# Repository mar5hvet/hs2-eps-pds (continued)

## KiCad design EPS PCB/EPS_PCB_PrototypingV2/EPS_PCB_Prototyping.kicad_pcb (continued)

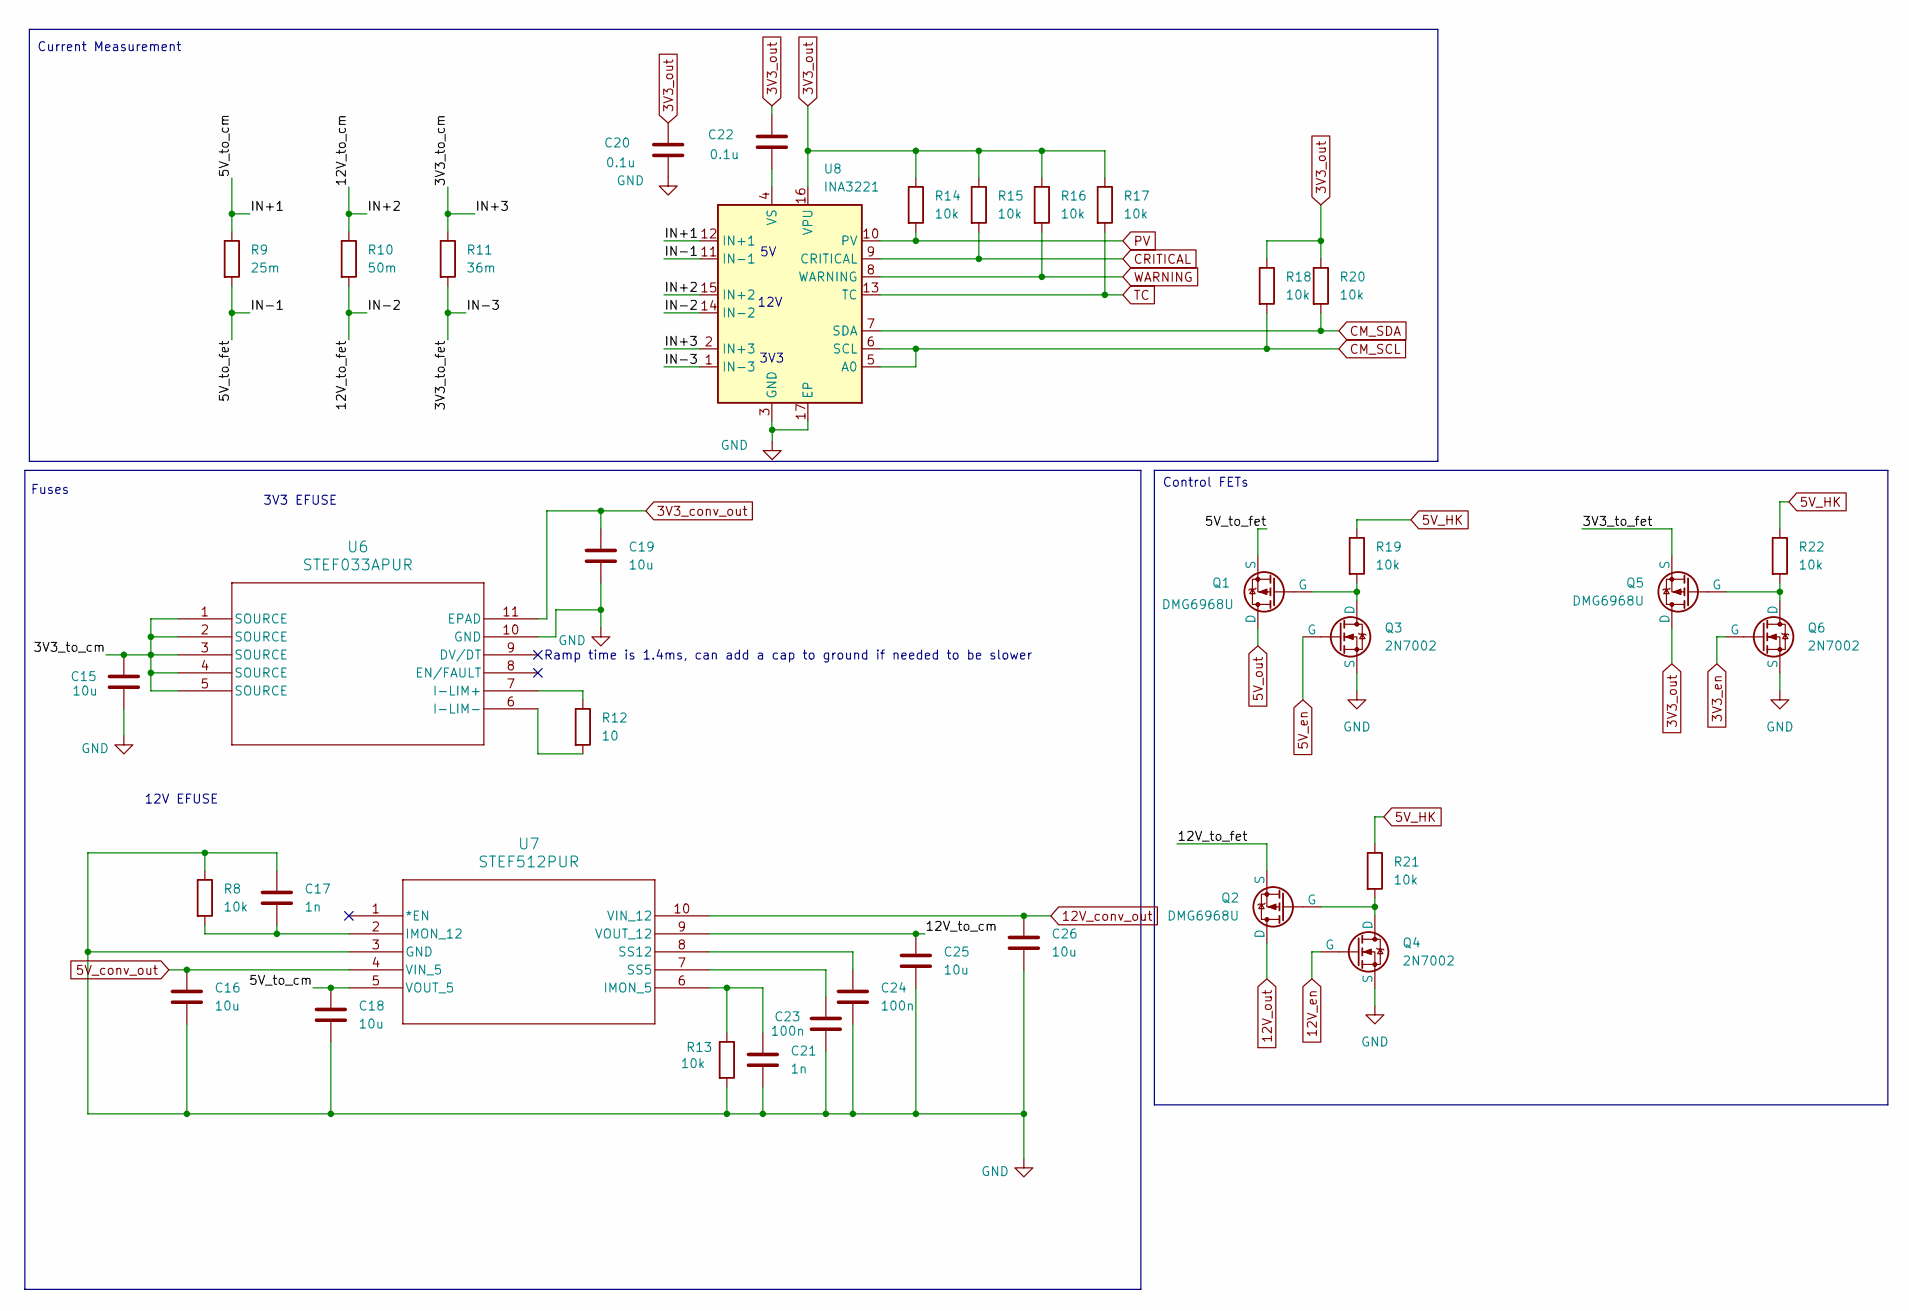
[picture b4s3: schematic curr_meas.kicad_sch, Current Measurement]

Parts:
C15, C16, C18, C19, C25, C26: 10u; C_0603_1608Metric
C17, C21: 1n; C_0603_1608Metric
C20, C22: 0.1u; C_0603_1608Metric
C23, C24: 100n; C_0603_1608Metric
Q1, Q2, Q5: DMG6968U; SOT-23-3
Q3, Q4, Q6: 2N7002; SOT-23-3
R8, R13, R14, R15, R16, R17, R18, R20: 10k; R_0603_1608Metric
R9: 25m; RES_VISHAY_WSLP2512_A_VIS
R10: 50m; RES_VISHAY_WSLP2512_A_VIS
R11: 36m; RES_VISHAY_WSLP2512_A_VIS
R12: 10; R_0603_1608Metric
R19, R21, R22: 10k; R_1206_3216Metric
U6: STEF033APUR; STEF033
U7: STEF512PUR; QFN10_2X3_STM-L
U8: INA3221; Texas_RGV0016A_VQFN-16-1EP_4x4mm_P0.65mm_EP2.1x2.1mm

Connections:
3V3_conv_out: C19.1, U6.11 (EPAD); also elsewhere on the board
3V3_en: Q6.2 (G); also elsewhere on the board
3V3_out: C20.1, C22.1, Q5.1 (D), R14.1, R15.1, R16.1, R17.1, R18.1, R20.1, U8.16 (VPU); also elsewhere on the board
5V_HK: R19.1, R21.1, R22.1; also elsewhere on the board
5V_conv_out: C16.1, U7.4 (VIN_5); also elsewhere on the board
5V_en: Q3.2 (G); also elsewhere on the board
5V_out: Q1.1 (D); also elsewhere on the board
12V_conv_out: C26.1, U7.10 (VIN_12); also elsewhere on the board
12V_en: Q4.2 (G); also elsewhere on the board
12V_out: Q2.1 (D); also elsewhere on the board
/Curr_meas/3V3_to_cm: C15.1, R11.1, U6.1 (SOURCE), U6.2 (SOURCE), U6.3 (SOURCE), U6.4 (SOURCE), U6.5 (SOURCE), U8.2 (IN+3)
/Curr_meas/3V3_to_fet: Q5.3 (S), R11.2, U8.1 (IN-3)
/Curr_meas/5V_to_cm: C18.1, R9.1, U7.5 (VOUT_5), U8.12 (IN+1)
/Curr_meas/5V_to_fet: Q1.3 (S), R9.2, U8.11 (IN-1)
/Curr_meas/12V_to_cm: C25.1, R10.1, U7.9 (VOUT_12), U8.15 (IN+2)
/Curr_meas/12V_to_fet: Q2.3 (S), R10.2, U8.14 (IN-2)
CM_SCL: R18.2, U8.5 (A0), U8.6 (SCL); also elsewhere on the board
CM_SDA: R20.2, U8.7 (SDA); also elsewhere on the board
CRITICAL: R15.2, U8.9 (CRITICAL); also elsewhere on the board
GND: C15.2, C16.2, C17.1, C18.2, C19.2, C20.2, C21.2, C23.2, C24.2, C25.2, C26.2, Q3.3 (S), Q4.3 (S), Q6.3 (S), R8.1, R13.2, U6.10 (GND), U7.3 (GND), U8.3 (GND), U8.17 (EP); also elsewhere on the board
unnamed: Q1.2 (G), Q3.1 (D), R19.2
unnamed: Q2.2 (G), Q4.1 (D), R21.2
unnamed: Q5.2 (G), Q6.1 (D), R22.2
unnamed: R12.1, U6.7 (I-LIM+)
unnamed: R12.2, U6.6 (I-LIM-)
unnamed: C21.1, R13.1, U7.6 (IMON_5)
unnamed: C17.2, R8.2, U7.2 (IMON_12)
unnamed: C23.1, U7.7 (SS5)
unnamed: C24.1, U7.8 (SS12)
unnamed: C22.2, U8.4 (VS)
PV: R14.2, U8.10 (PV); also elsewhere on the board
TC: R17.2, U8.13 (TC)
WARNING: R16.2, U8.8 (WARNING); also elsewhere on the board

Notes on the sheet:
12V
Current Measurement
3V3 EFUSE
3V3
Ramp time is 1.4ms, can add a cap to ground if needed to be slower
12V EFUSE
Control FETs
Fuses

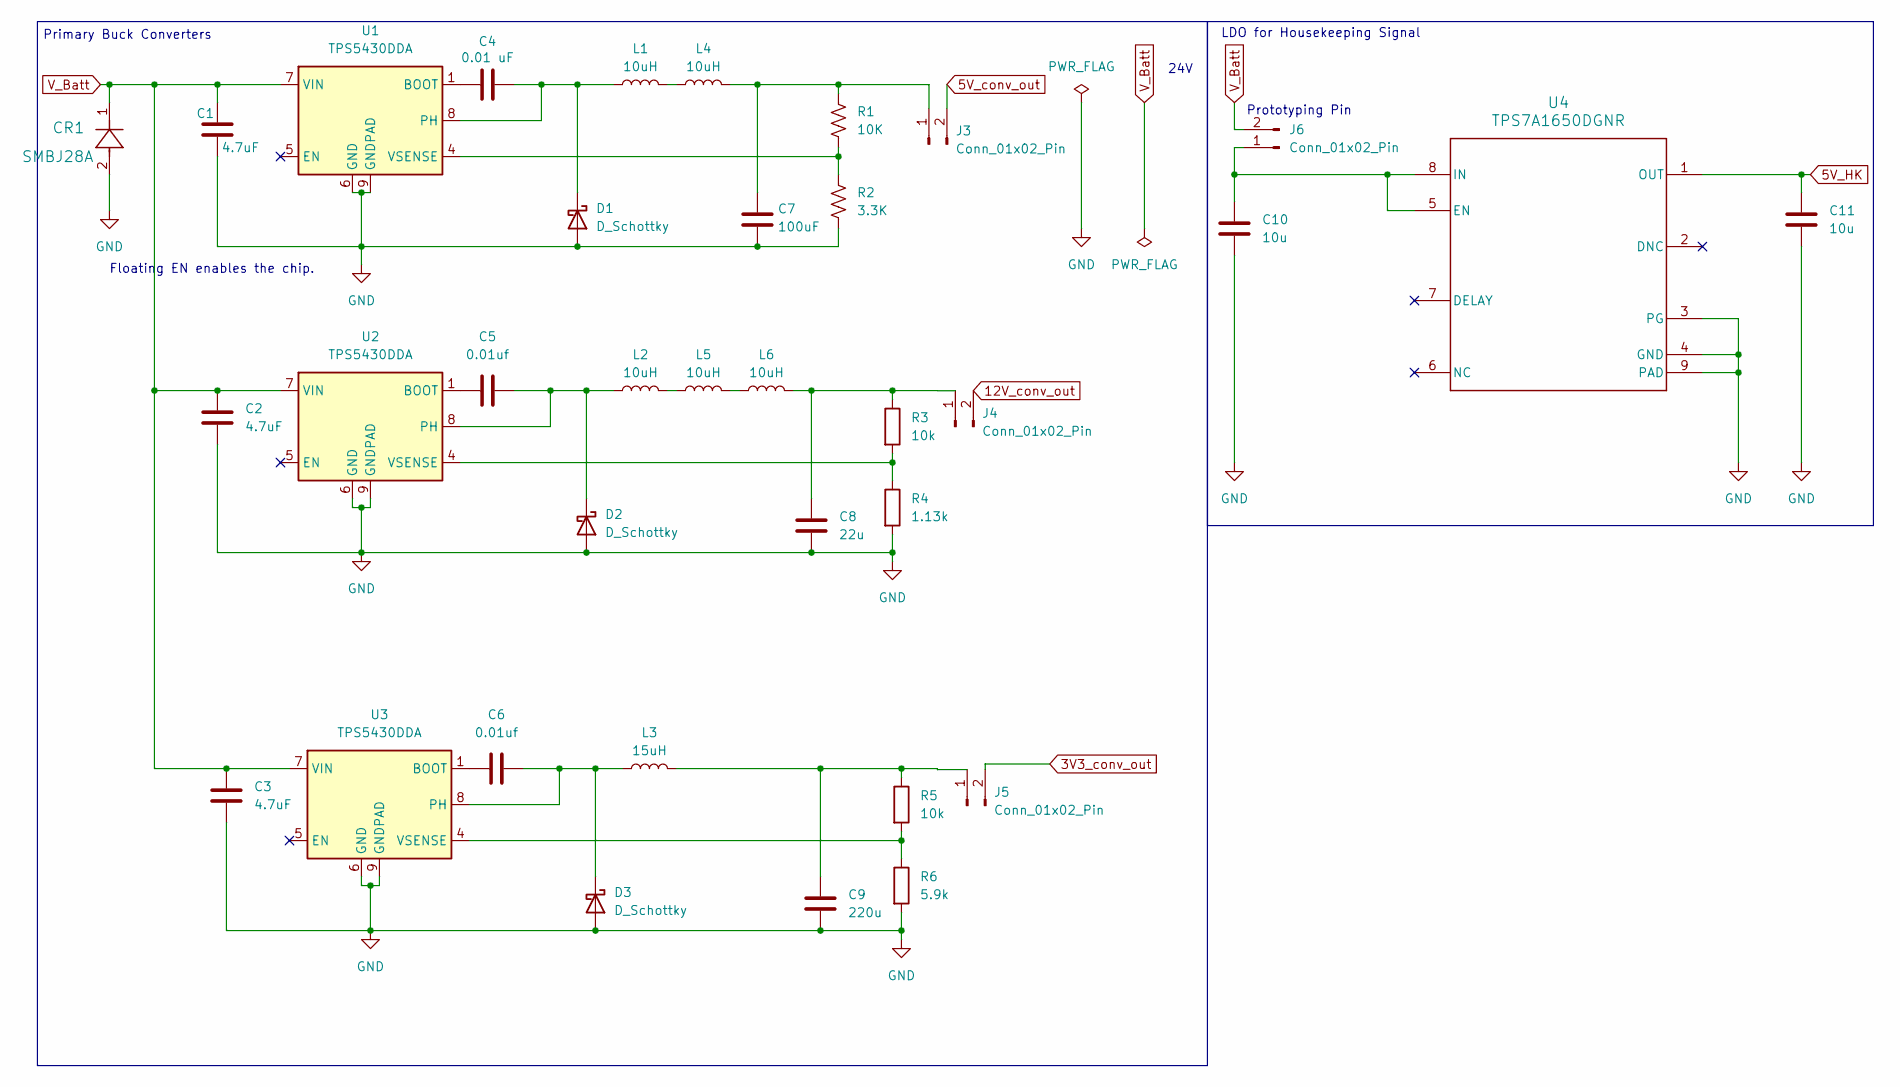
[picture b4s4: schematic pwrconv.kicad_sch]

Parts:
C1, C2, C3: 4.7uF; C_0805_2012Metric; LCSC C1779
C4: 0.01 uF; C_0603_1608Metric; LCSC C1589
C5, C6: 0.01uf; C_0603_1608Metric; LCSC C1589
C7: 100uF; C_0805_2012Metric; LCSC C2836437
C8: 22u; C_0805_2012Metric; LCSC C45783
C9: 220u; C_0805_2012Metric; LCSC C125977
C10, C11: 10u; C_0603_1608Metric
CR1: SMBJ28A; DIODE_DO214AA
D1, D2, D3: D_Schottky; D_SOD-323; LCSC C191023
J3, J4, J5, J6: Conn_01x02_Pin; PinSocket_1x02_P2.54mm_Vertical
L1, L2, L4, L5, L6: 10uH; L_Changjiang_FXL0630; LCSC C167223
L3: 15uH; L_Changjiang_FXL0630; LCSC C40000
R1: 10K; R_0603_1608Metric; LCSC C15401
R2: 3.3K; R_1206_3216Metric; LCSC C26041
R3, R5: 10k; R_0603_1608Metric; LCSC C15401
R4: 1.13k; R_1206_3216Metric; LCSC C4410
R6: 5.9k; R_1206_3216Metric; LCSC C488883
U1, U2, U3: TPS5430DDA; TI_SO-PowerPAD-8_ThermalVias; LCSC C9864
U4: TPS7A1650DGNR; DGN0008C_N

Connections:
3V3_conv_out: J5.2; also elsewhere on the board
5V_HK: C11.2, U4.1 (OUT); also elsewhere on the board
5V_conv_out: J3.2; also elsewhere on the board
12V_conv_out: J4.2; also elsewhere on the board
GND: C1.2, C2.2, C3.2, C7.2, C8.1, C9.1, C10.1, C11.1, CR1.2, D1.2 (A), D2.2 (A), D3.2 (A), R2.2, R4.2, R6.2, U1.6 (GND), U1.9 (GNDPAD), U2.6 (GND), U2.9 (GNDPAD), U3.6 (GND), U3.9 (GNDPAD), U4.3 (PG), U4.4 (GND), U4.9 (PAD), U4.V; also elsewhere on the board
unnamed: C4.2, D1.1 (K), L1.1, U1.8 (PH)
unnamed: C5.2, D2.1 (K), L2.1, U2.8 (PH)
unnamed: C6.2, D3.1 (K), L3.1, U3.8 (PH)
unnamed: C7.1, J3.1, L4.2, R1.1
unnamed: C8.2, J4.1, L6.2, R3.1
unnamed: C9.2, J5.1, L3.2, R5.1
unnamed: C10.2, J6.1, U4.5 (EN), U4.8 (IN)
unnamed: L1.2, L4.1
unnamed: L2.2, L5.1
unnamed: L5.2, L6.1
unnamed: C4.1, U1.1 (BOOT)
unnamed: R1.2, R2.1, U1.4 (VSENSE)
unnamed: C5.1, U2.1 (BOOT)
unnamed: R3.2, R4.1, U2.4 (VSENSE)
unnamed: C6.1, U3.1 (BOOT)
unnamed: R5.2, R6.1, U3.4 (VSENSE)
V_Batt: C1.1, C2.1, C3.1, CR1.1, J6.2, U1.7 (VIN), U2.7 (VIN), U3.7 (VIN); also elsewhere on the board

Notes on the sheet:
Primary Buck Converters
LDO for Housekeeping Signal
Prototyping Pin
24V
Floating EN enables the chip.

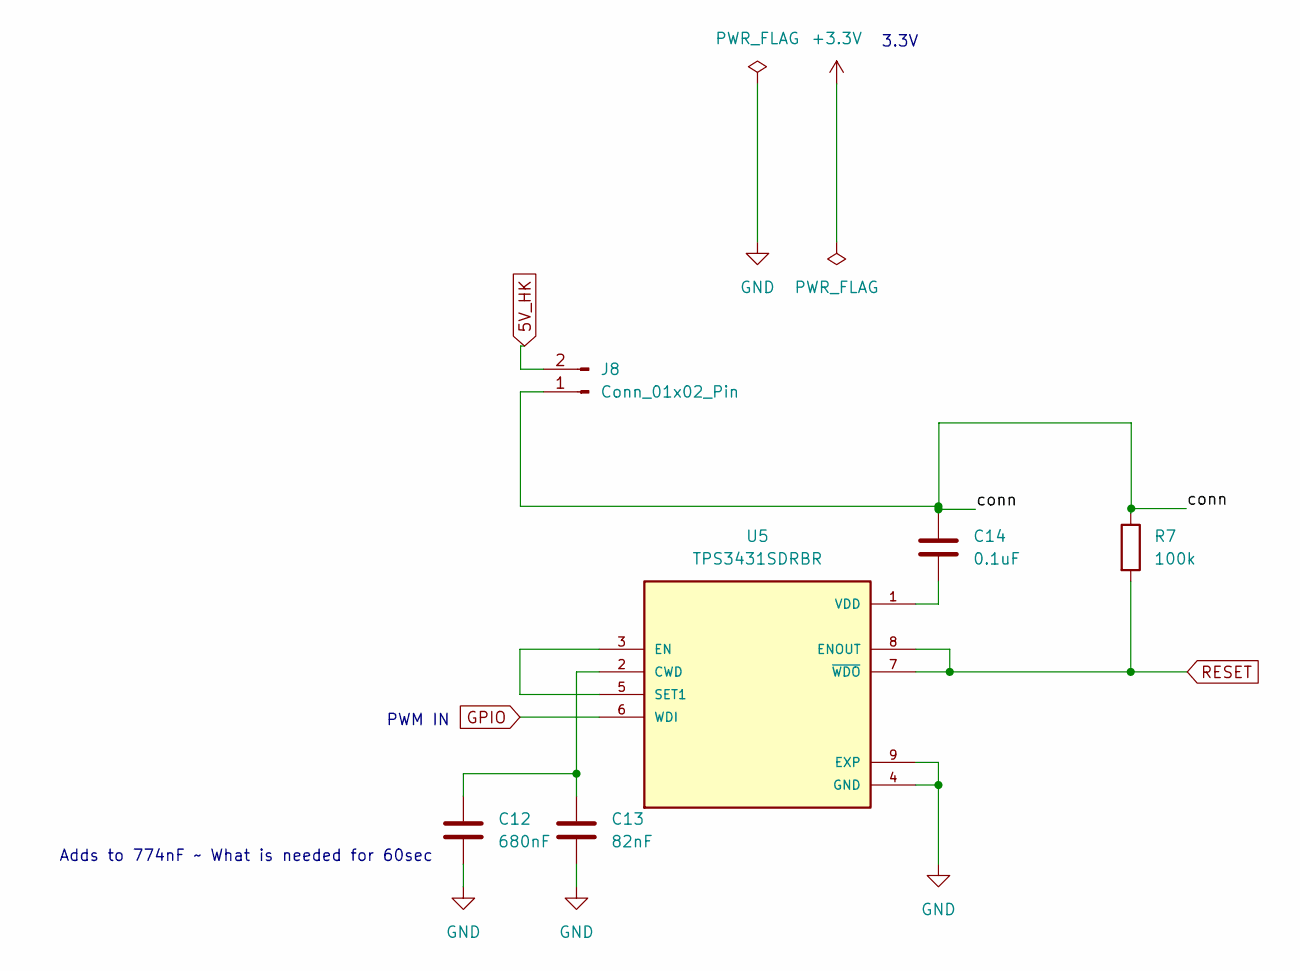
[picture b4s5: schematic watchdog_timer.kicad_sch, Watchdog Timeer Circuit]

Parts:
C12: 680nF; C_1206_3216Metric
C13: 82nF; C_1206_3216Metric
C14: 0.1uF; C_0603_1608Metric
J8: Conn_01x02_Pin; PinSocket_1x02_P2.54mm_Vertical
R7: 100k; R_1206_3216Metric
U5: TPS3431SDRBR; IC_TPS3431SDRBR; PARTREV A

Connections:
5V_HK: J8.2; also elsewhere on the board
/watchdog_timer/conn: C14.1, J8.1, R7.1
GND: C12.2, C13.2, U5.4 (GND), U5.9 (EXP), U5.10, U5.11, U5.12, U5.13; also elsewhere on the board
GPIO: U5.6 (WDI); also elsewhere on the board
unnamed: C12.1, C13.1, U5.2 (CWD)
unnamed: U5.3 (EN), U5.5 (SET1)
unnamed: C14.2, U5.1 (VDD)
RESET: R7.2, U5.7 (~WDO), U5.8 (ENOUT); also elsewhere on the board

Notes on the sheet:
PWM IN
3.3V
Adds to 774nF ~ What is needed for 60sec

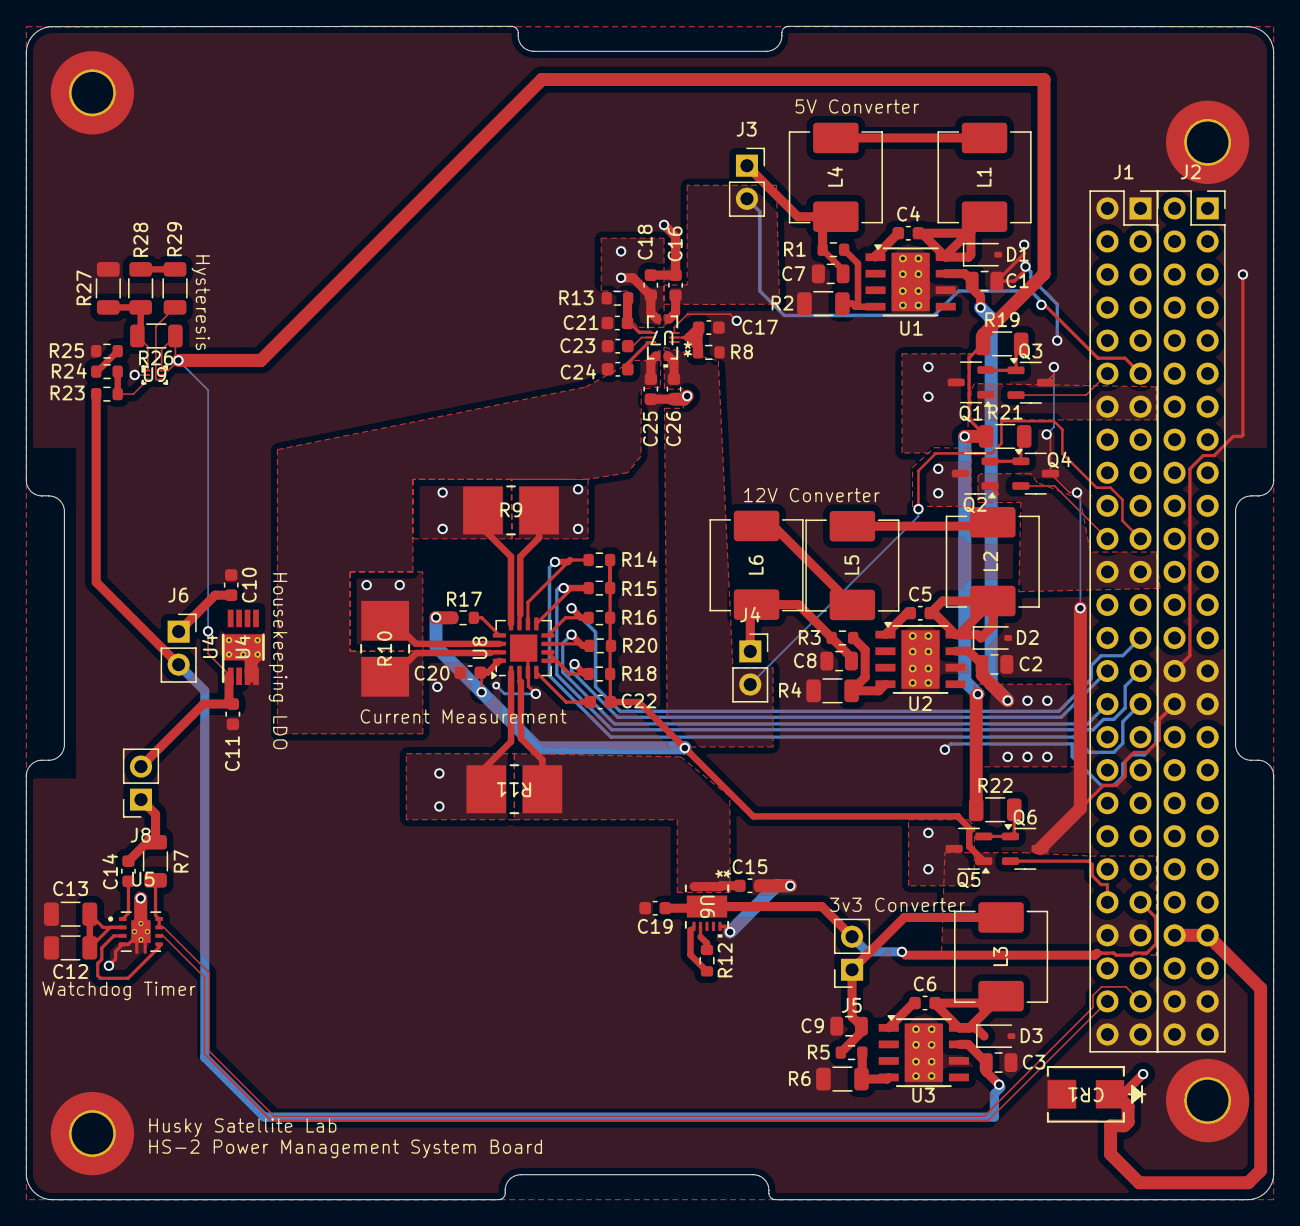
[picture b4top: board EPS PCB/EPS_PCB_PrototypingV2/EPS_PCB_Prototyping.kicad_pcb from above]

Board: 2 copper layers, 95.9 x 90.2 mm, 91 parts (0 on the bottom side), 61 nets.

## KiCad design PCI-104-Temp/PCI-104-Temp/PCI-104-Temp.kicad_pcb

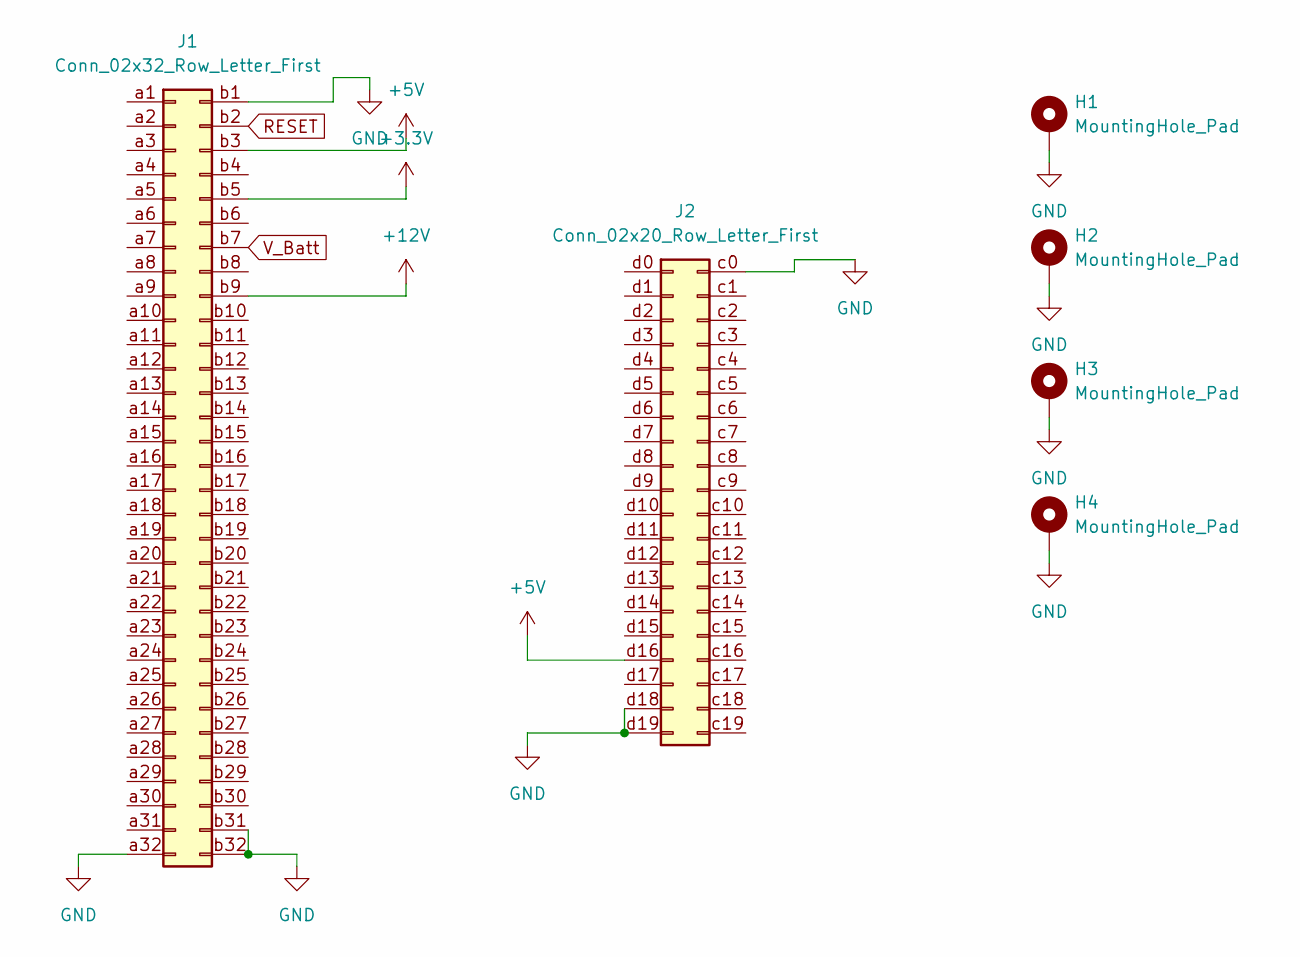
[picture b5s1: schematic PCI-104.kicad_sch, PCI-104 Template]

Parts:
H1, H2, H3, H4: MountingHole_Pad; MountingHole_3.2mm_M3_Pad
J1: Conn_02x32_Row_Letter_First; PinSocket_2x32_P2.54mm_Vertical
J2: Conn_02x20_Row_Letter_First; PinSocket_2x20_P2.54mm_Vertical

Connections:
+3.3V: J1.b5
+5V: J1.b3, J2.d16
+12V: J1.b9
GND: H1.1, H2.1, H3.1, H4.1, J1.a32, J1.b1, J1.b31, J1.b32, J2.c0, J2.d18, J2.d19
RESET: J1.b2
V_Batt: J1.b7

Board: 2 copper layers, 6 parts (0 on the bottom side), 2 nets, no tracks yet.

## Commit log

2025-10-18 names to schematic
2025-10-25 added 3.3v converter
2025-10-29 added footprints to 3.3v
2025-11-07 Added Watchdog files
    Watchdog timer kicad Schematic
2025-11-16 EPS PCB Added
    - Added Heirarchal Project for the Main PDS Board
    - Added PCI-104 Template PCB
2025-11-21 PDR Update
    Added Current Measurement, Hysteresis, EFuses
2026-01-31 Prototyping Board Added
2026-02-12 Prototype board v1 finished
2026-02-19 EPS PCB Prototype For order
    yea
2026-03-01 PC104 Template Updated
2026-04-06 PCI-104 Template Updated to Follow Librecube
2026-04-09 PC-104 Template Upadte
2026-04-17 PC104 Template Updates
2026-04-27 Cloning of OLD HS2-PDS Repository
2026-04-27 HS2 Update
